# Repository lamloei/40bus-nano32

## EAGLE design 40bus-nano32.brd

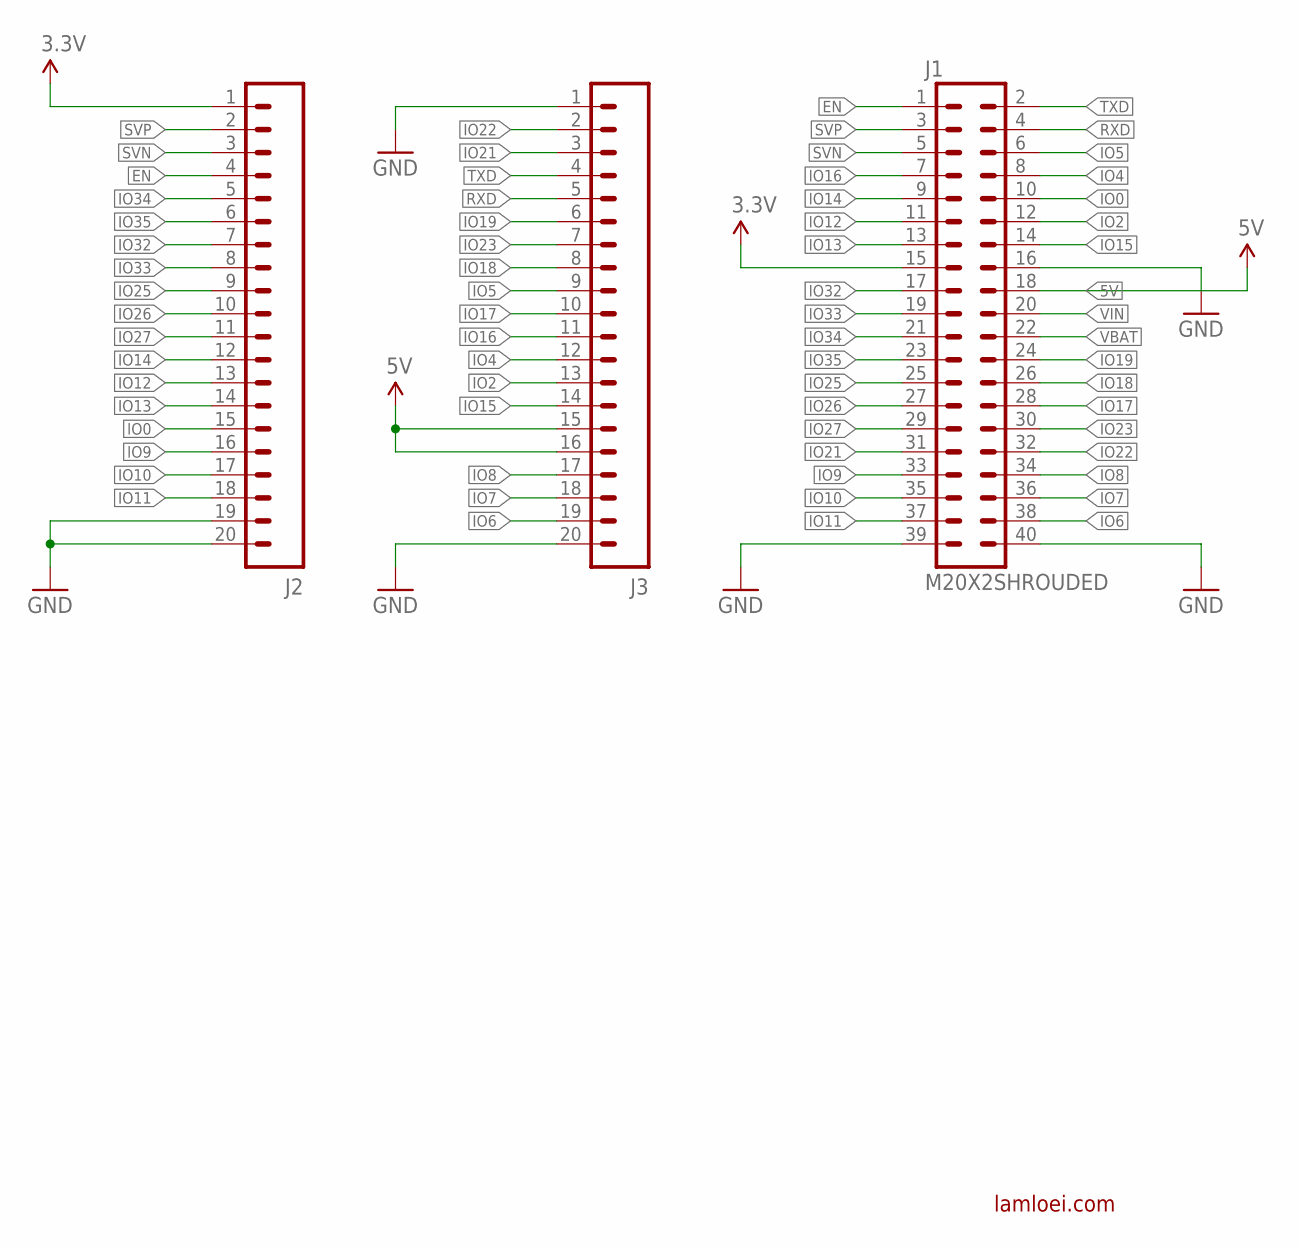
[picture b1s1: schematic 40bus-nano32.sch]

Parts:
J1: M20X2SHROUDED; 2X20_SHROUDED
J2, J3: M20; 1X20
U$1: LAMLEOI_LOGO_3

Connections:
3.3V: J1.15, J2.1
5V: J1.18, J3.15, J3.16
EN: J1.1, J2.4
GND: J1.16, J1.39, J1.40, J2.19, J2.20, J3.1, J3.20
IO0: J1.10, J2.15
IO2: J1.12, J3.13
IO4: J1.8, J3.12
IO5: J1.6, J3.9
IO6: J1.38, J3.19
IO7: J1.36, J3.18
IO8: J1.34, J3.17
IO9: J1.33, J2.16
IO10: J1.35, J2.17
IO11: J1.37, J2.18
IO12: J1.11, J2.13
IO13: J1.13, J2.14
IO14: J1.9, J2.12
IO15: J1.14, J3.14
IO16: J1.7, J3.11
IO17: J1.28, J3.10
IO18: J1.26, J3.8
IO19: J1.24, J3.6
IO21: J1.31, J3.3
IO22: J1.32, J3.2
IO23: J1.30, J3.7
IO25: J1.25, J2.9
IO26: J1.27, J2.10
IO27: J1.29, J2.11
IO32: J1.17, J2.7
IO33: J1.19, J2.8
IO34: J1.21, J2.5
IO35: J1.23, J2.6
RXD: J1.4, J3.5
SVN: J1.5, J2.3
SVP: J1.3, J2.2
TXD: J1.2, J3.4
VBAT: J1.22
VIN: J1.20

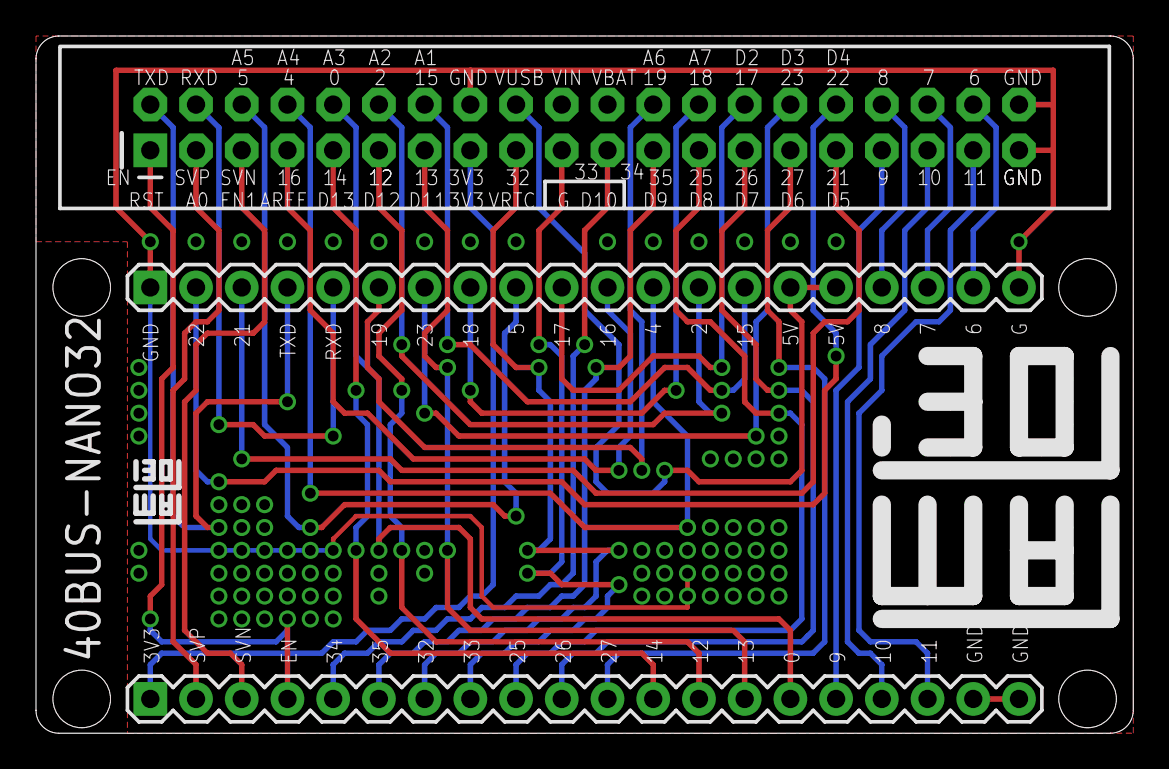
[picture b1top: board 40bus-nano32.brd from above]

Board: 2 copper layers, 61.0 x 38.7 mm, 5 parts (1 on the bottom side), 36 nets.

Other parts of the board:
U$2: LAMLEOI_LOGO_3

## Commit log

2016-10-24 :tada: Added .gitattributes & .gitignore files
2016-10-24 40bus-nano32
    40bus-nano32

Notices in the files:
parts and their libraries:
SparkFun-Connectors: Licensing: Creative Commons ShareAlike 4.0 International - https://creativecommons.org/licenses/by-sa/4.0
